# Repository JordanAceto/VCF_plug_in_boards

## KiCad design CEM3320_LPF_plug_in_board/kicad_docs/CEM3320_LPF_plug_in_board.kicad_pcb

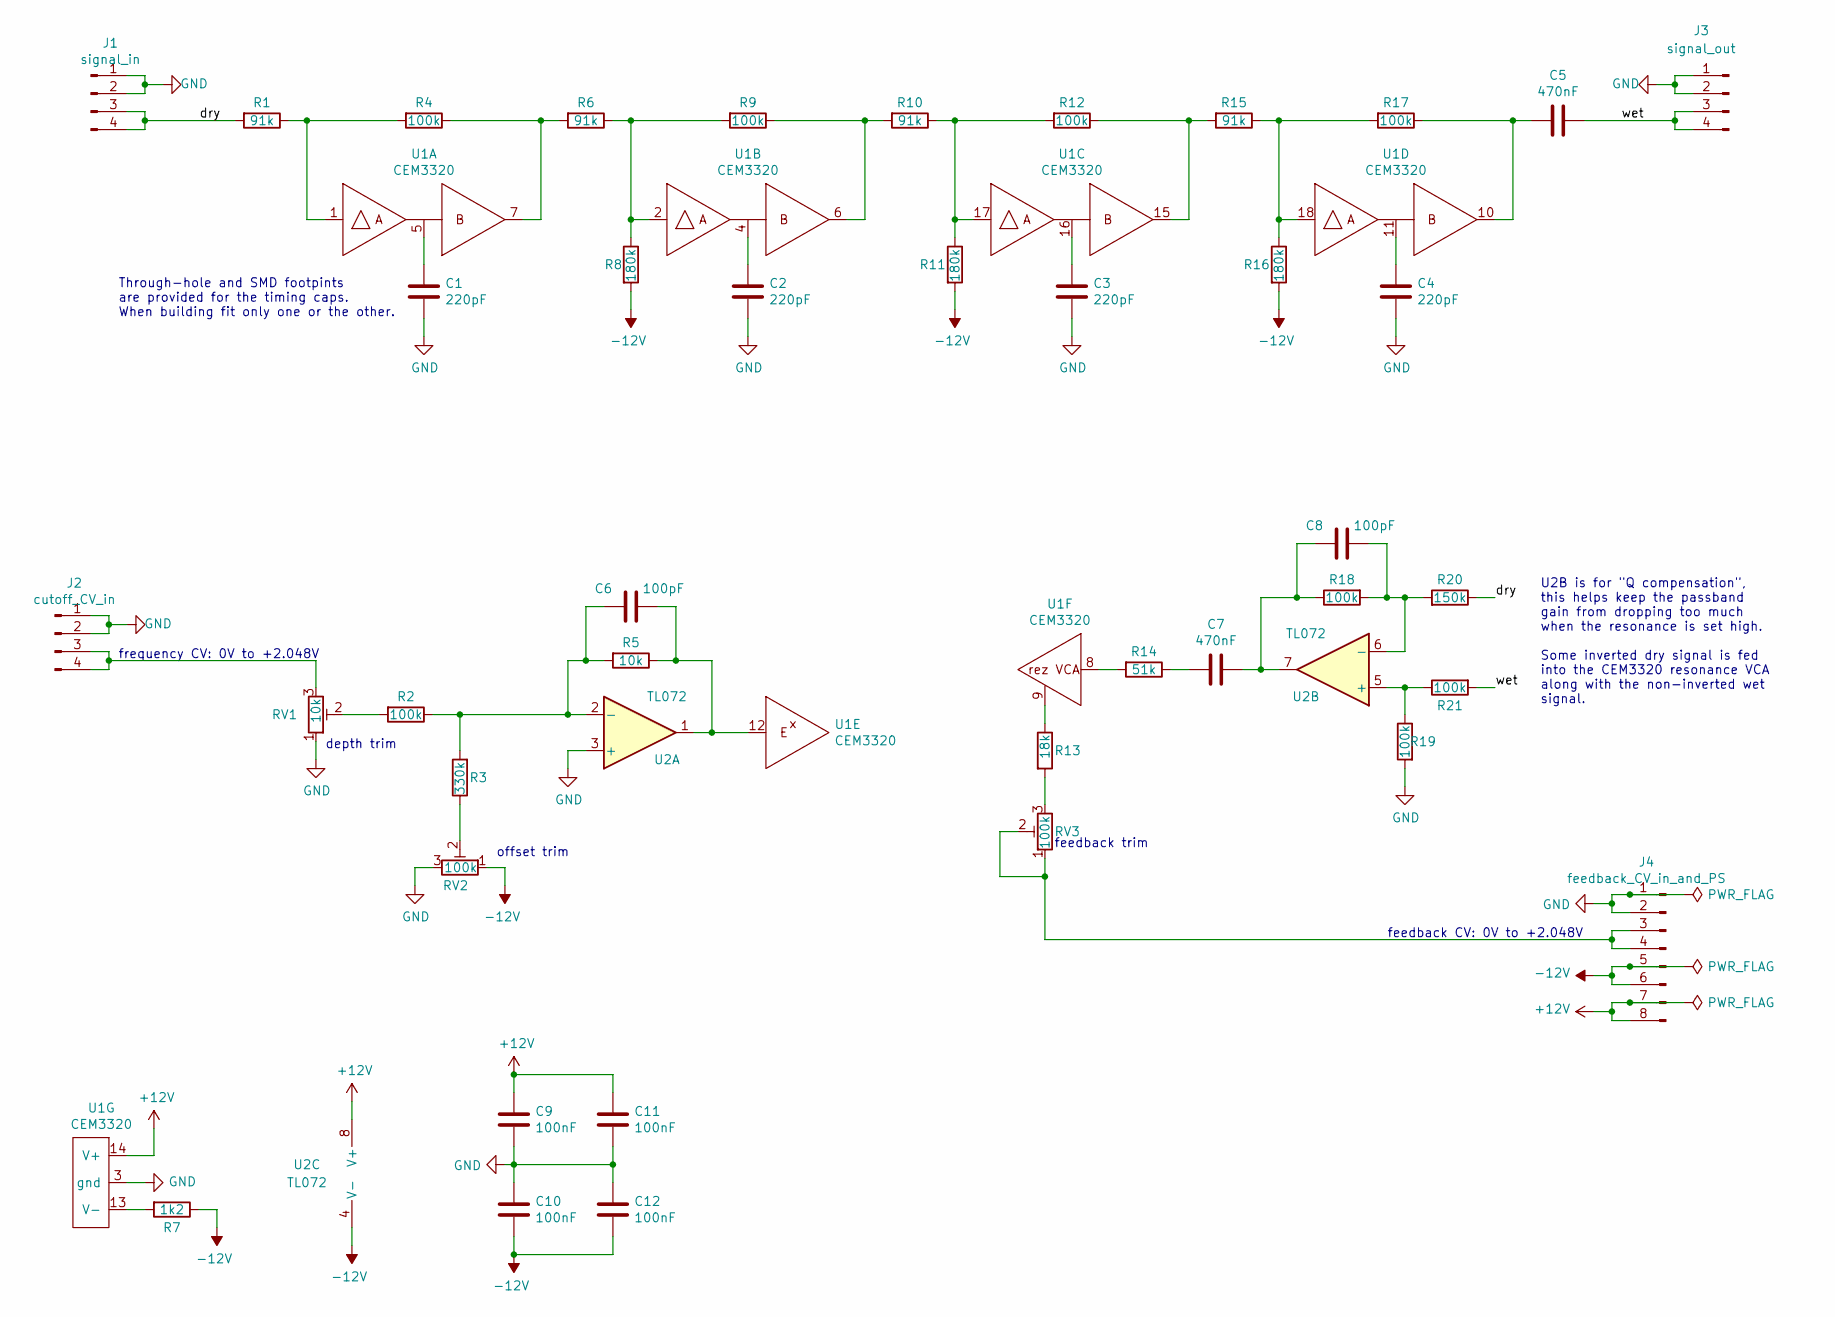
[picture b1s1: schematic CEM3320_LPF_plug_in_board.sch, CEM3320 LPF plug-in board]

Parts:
C1, C2, C3, C4: 220pF; timing_cap_dual_fp
C5, C7: 470nF; C_Rect_L7.0mm_W3.5mm_P5.00mm
C6, C8: 100pF; C_0805_2012Metric_Pad1.15x1.40mm_HandSolder
C9, C10, C11, C12: 100nF; C_0805_2012Metric_Pad1.15x1.40mm_HandSolder
J1: signal_in; PinHeader_1x04_P2.54mm_Vertical
J2: cutoff_CV_in; PinHeader_1x04_P2.54mm_Vertical
J3: signal_out; PinHeader_1x04_P2.54mm_Vertical
J4: feedback_CV_in_and_PS; PinHeader_1x08_P2.54mm_Vertical
R1, R6, R10, R15: 91k; R_0805_2012Metric_Pad1.15x1.40mm_HandSolder
R2, R4, R9, R12, R17, R18, R19, R21: 100k; R_0805_2012Metric_Pad1.15x1.40mm_HandSolder
R3: 330k; R_0805_2012Metric_Pad1.15x1.40mm_HandSolder
R5: 10k; R_0805_2012Metric_Pad1.15x1.40mm_HandSolder
R7: 1k2; R_0805_2012Metric_Pad1.15x1.40mm_HandSolder
R8, R11, R16: 180k; R_0805_2012Metric_Pad1.15x1.40mm_HandSolder
R13: 18k; R_0805_2012Metric_Pad1.15x1.40mm_HandSolder
R14: 51k; R_0805_2012Metric_Pad1.15x1.40mm_HandSolder
R20: 150k; R_0805_2012Metric_Pad1.15x1.40mm_HandSolder
RV1: 10k; Potentiometer_Bourns_3296W_Vertical
RV2, RV3: 100k; Potentiometer_Bourns_3296W_Vertical
U1: CEM3320; DIP-18_W7.62mm
U2: TL072; SOIC-8_3.9x4.9mm_P1.27mm

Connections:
+12V: C9.1, C11.1, J4.7, J4.8, U1.14 (V+), U2.8 (V+)
-12V: C10.2, C12.2, J4.5, J4.6, R7.1, R8.2, R11.2, R16.2, RV2.1, U2.4 (V-)
/dry: J1.3, J1.4, R1.2, R20.1
/wet: C5.1, J3.3, J3.4, R21.2
GND: C1.2, C2.2, C3.2, C4.2, C9.2, C10.1, C11.2, C12.1, J1.1, J1.2, J2.1, J2.2, J3.1, J3.2, J4.1, J4.2, R19.2, RV1.1, RV2.3, U1.3 (gnd), U2.3 (+)
unnamed: C1.1, U1.5
unnamed: C2.1, U1.4
unnamed: C3.1, U1.16
unnamed: C4.1, U1.11
unnamed: C5.2, R17.1, U1.10
unnamed: C6.1, R2.1, R3.2, R5.2, U2.2 (-)
unnamed: C6.2, R5.1, U1.12, U2.1
unnamed: C7.1, C8.1, R18.1, U2.7
unnamed: C7.2, R14.1
unnamed: C8.2, R18.2, R20.2, U2.6 (-)
unnamed: J2.3, J2.4, RV1.3
unnamed: J4.3, J4.4, RV3.1, RV3.2
unnamed: R1.1, R4.2, U1.1
unnamed: R2.2, RV1.2
unnamed: R3.1, RV2.2
unnamed: R4.1, R6.2, U1.7
unnamed: R6.1, R8.1, R9.2, U1.2
unnamed: R7.2, U1.13 (V-)
unnamed: R10.1, R11.1, R12.2, U1.17
unnamed: R9.1, R10.2, U1.6
unnamed: R12.1, R15.2, U1.15
unnamed: R13.1, U1.9
unnamed: R13.2, RV3.3
unnamed: R14.2, U1.8
unnamed: R15.1, R16.1, R17.2, U1.18
unnamed: R19.1, R21.1, U2.5 (+)

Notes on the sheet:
feedback CV: 0V to +2.048V
frequency CV: 0V to +2.048V
U2B is for "Q compensation", this helps keep the passband gain from dropping too much when the resonance is set high. Some inverted dry signal is fed into the CEM3320 resonance VCA along with the non-inverted wet signal.
feedback trim
depth trim
offset trim
Through-hole and SMD footpints are provided for the timing caps. When building fit only one or the other.

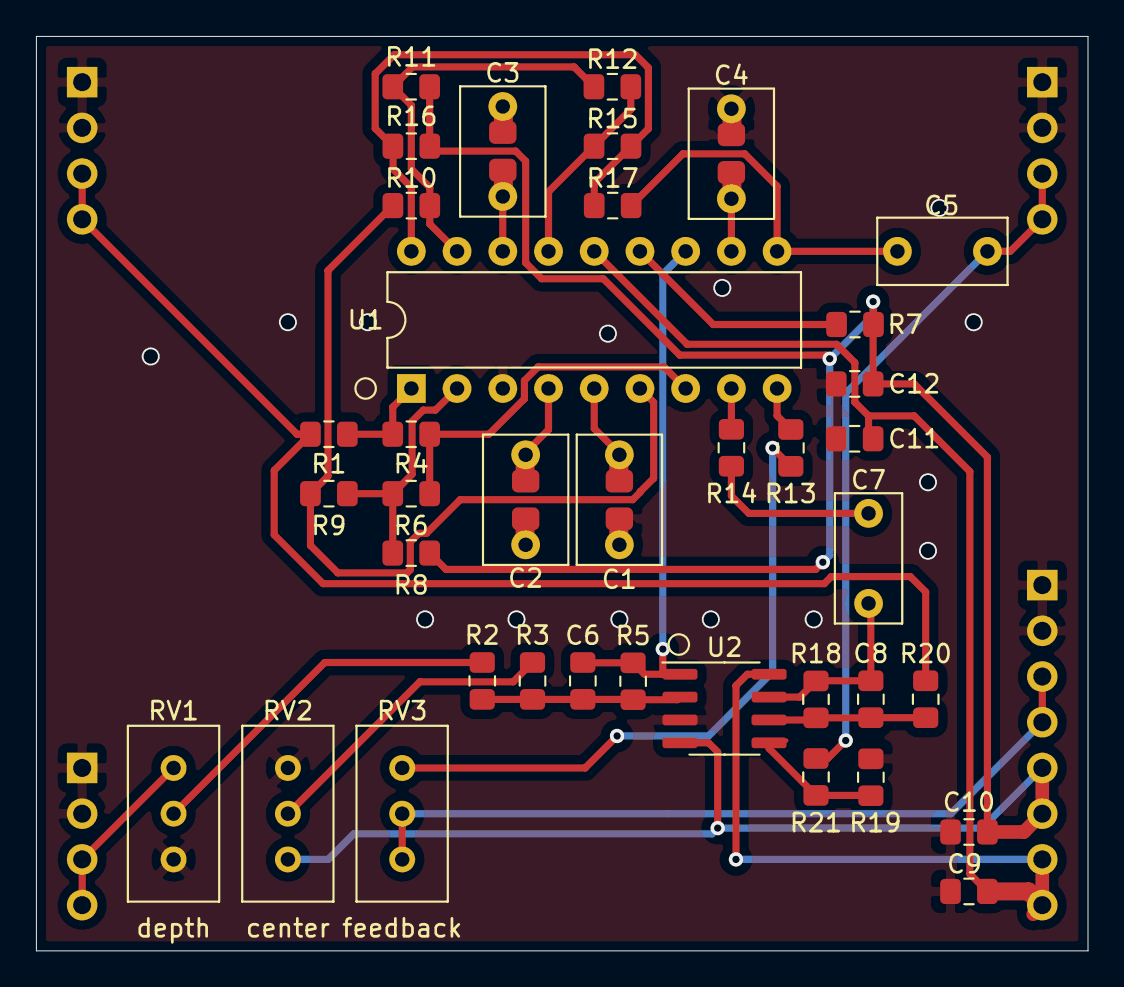
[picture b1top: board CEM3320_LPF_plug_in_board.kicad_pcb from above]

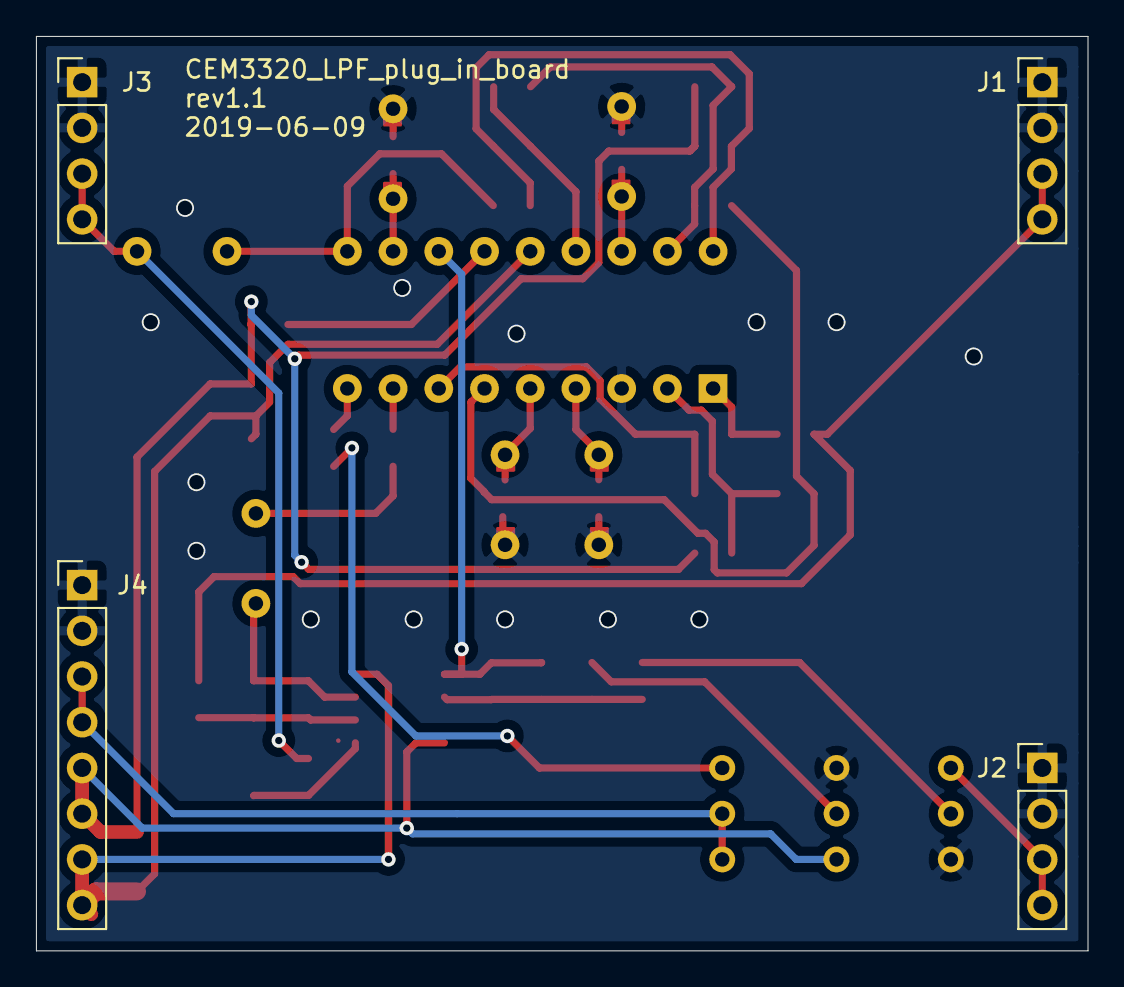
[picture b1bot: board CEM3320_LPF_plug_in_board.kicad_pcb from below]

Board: 2 copper layers, 58.4 x 50.8 mm, 42 parts (4 on the bottom side), 31 nets.

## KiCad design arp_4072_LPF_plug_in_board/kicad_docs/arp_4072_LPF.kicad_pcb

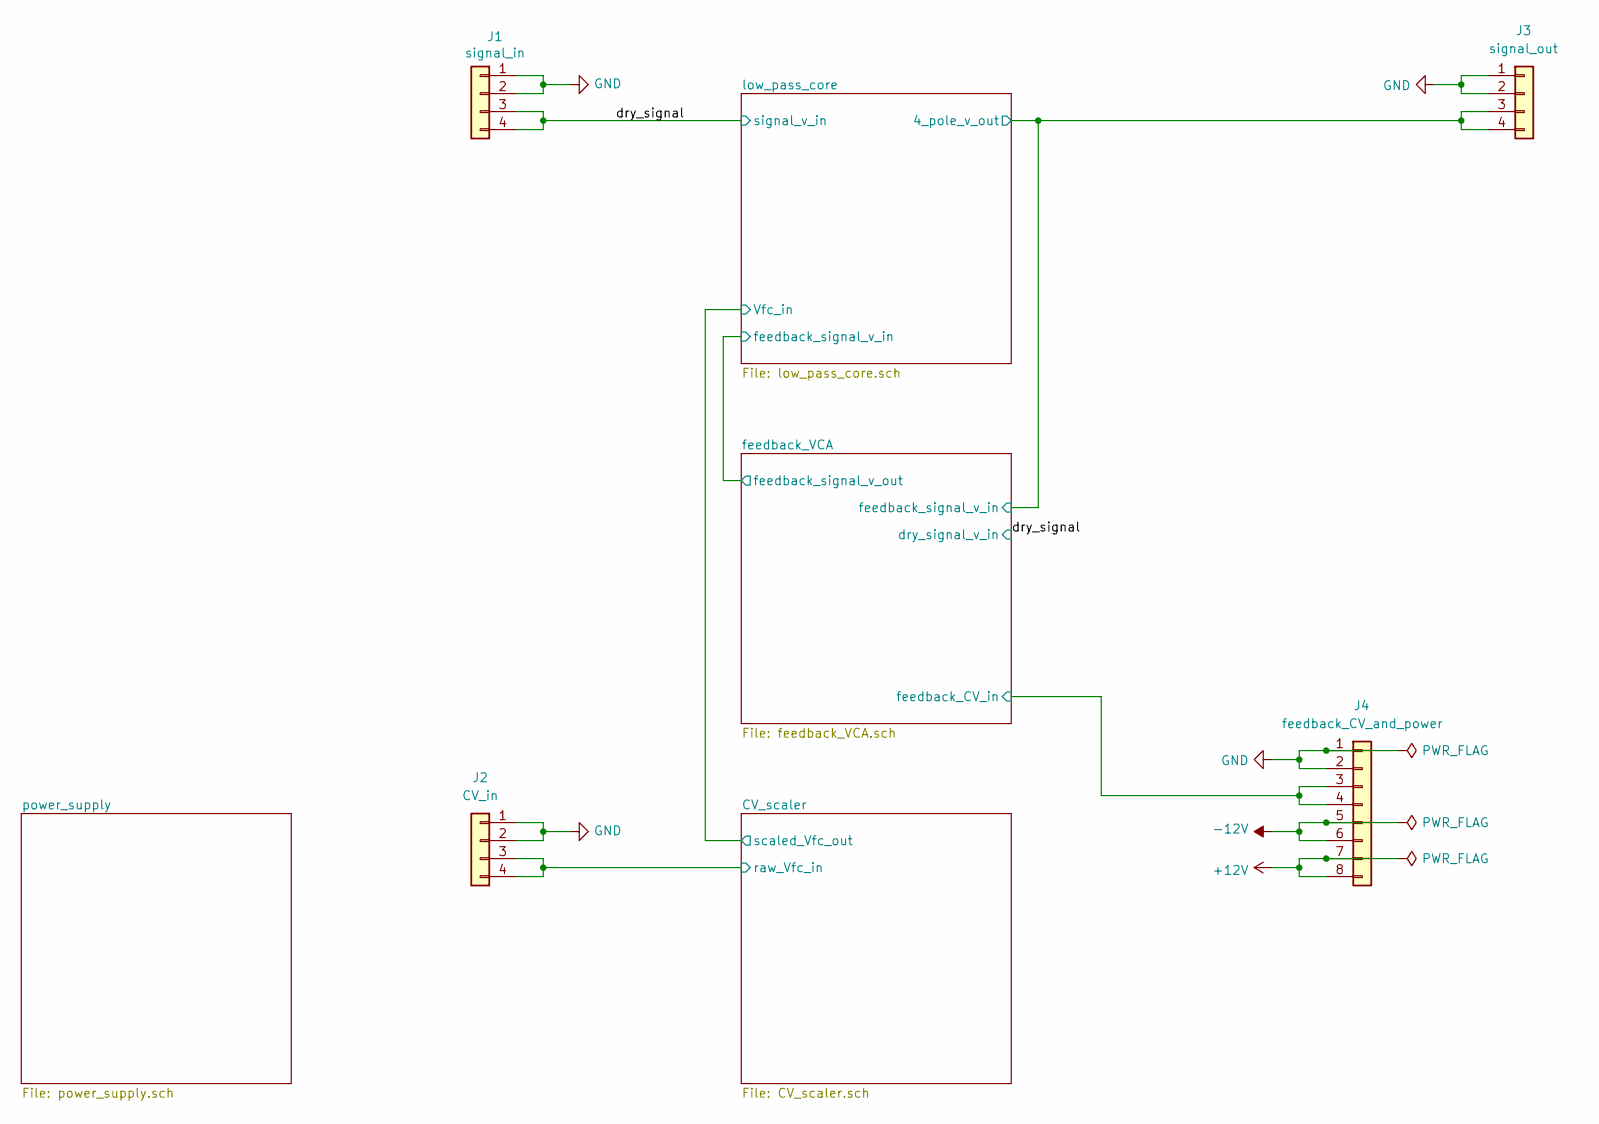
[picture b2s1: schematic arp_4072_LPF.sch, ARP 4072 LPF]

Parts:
J1: signal_in; PinHeader_1x04_P2.54mm_Vertical
J2: CV_in; PinHeader_1x04_P2.54mm_Vertical
J3: signal_out; PinHeader_1x04_P2.54mm_Vertical
J4: feedback_CV_and_power; PinHeader_1x08_P2.54mm_Vertical

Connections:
+12V: J4.7, J4.8; also elsewhere on the board
-12V: J4.5, J4.6; also elsewhere on the board
/CV_scaler/raw_Vfc_in: J2.3, J2.4; also elsewhere on the board
/dry_signal: J1.3, J1.4; also elsewhere on the board
/feedback_VCA/feedback_CV_in: J4.3, J4.4; also elsewhere on the board
/low_pass_core/4_pole_v_out: J3.3, J3.4; also elsewhere on the board
GND: J1.1, J1.2, J2.1, J2.2, J3.1, J3.2, J4.1, J4.2; also elsewhere on the board

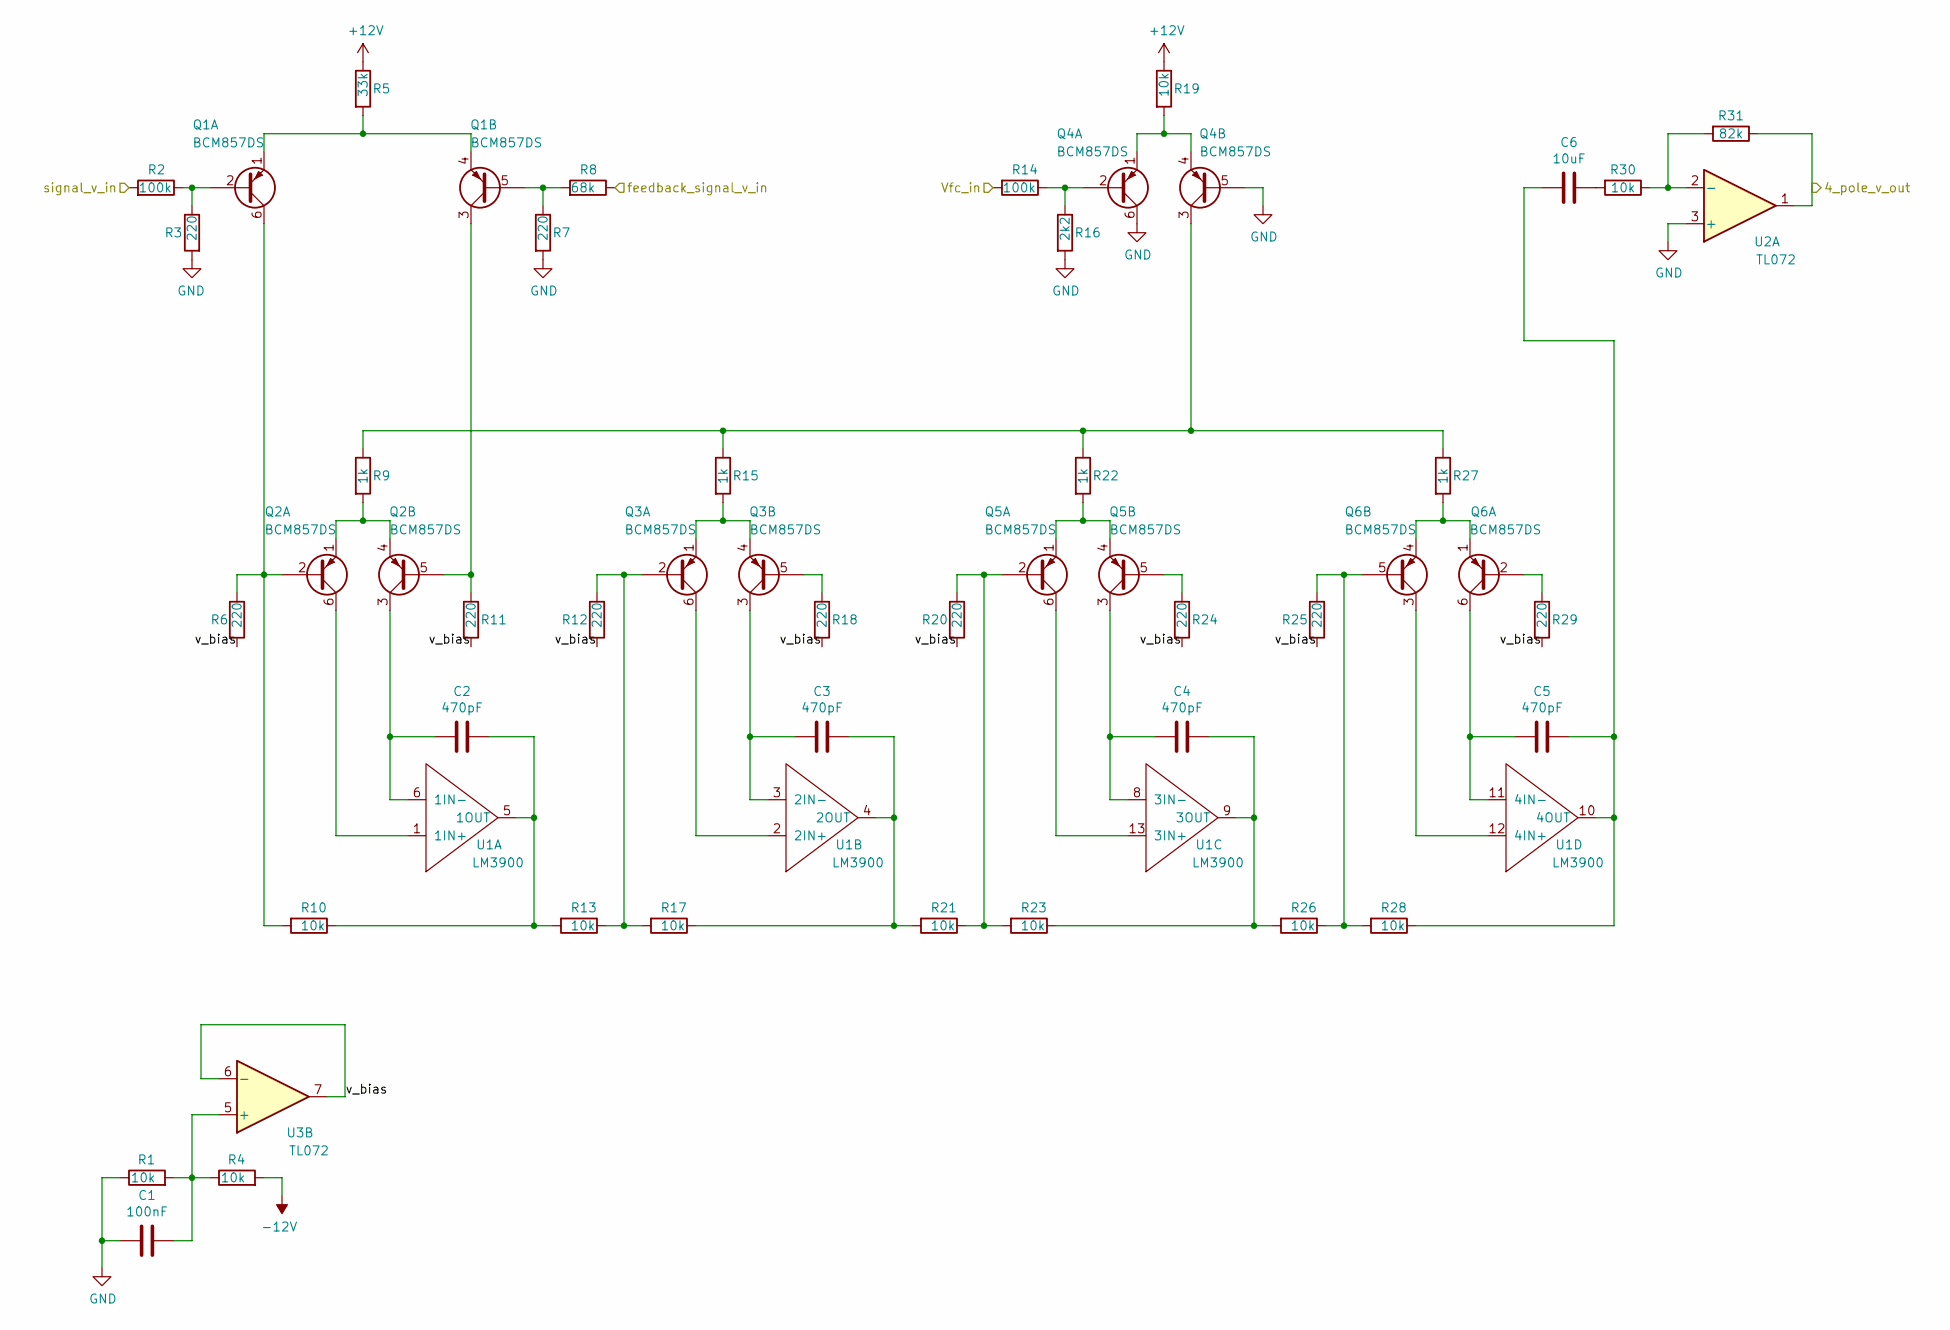
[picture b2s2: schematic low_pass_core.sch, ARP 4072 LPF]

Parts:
C1: 100nF; C_0805_2012Metric_Pad1.15x1.40mm_HandSolder
C2, C3, C4, C5: 470pF; C_0805_2012Metric_Pad1.15x1.40mm_HandSolder
C6: 10uF; CP_Radial_D6.3mm_P2.50mm
Q1, Q2, Q3, Q4, Q5, Q6: BCM857DS; SOT457
R1, R4, R10, R13, R17, R19, R21, R23, R26, R28, R30: 10k; R_0805_2012Metric_Pad1.15x1.40mm_HandSolder
R2, R14: 100k; R_0805_2012Metric_Pad1.15x1.40mm_HandSolder
R3, R6, R7, R11, R12, R18, R20, R24, R25, R29: 220; R_0805_2012Metric_Pad1.15x1.40mm_HandSolder
R5: 33k; R_0805_2012Metric_Pad1.15x1.40mm_HandSolder
R8: 68k; R_0805_2012Metric_Pad1.15x1.40mm_HandSolder
R9, R15, R22, R27: 1k; R_0805_2012Metric_Pad1.15x1.40mm_HandSolder
R16: 2k2; R_0805_2012Metric_Pad1.15x1.40mm_HandSolder
R31: 82k; R_0805_2012Metric_Pad1.15x1.40mm_HandSolder
U1: LM3900; SOIC-14_3.9x8.7mm_P1.27mm
U2, U3: TL072; SOIC-8_3.9x4.9mm_P1.27mm

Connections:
+12V: R5.1, R19.1; also elsewhere on the board
-12V: R4.2; also elsewhere on the board
/dry_signal: R2.2; also elsewhere on the board
/low_pass_core/4_pole_v_out: R31.1, U2.1; also elsewhere on the board
/low_pass_core/Vfc_in: R14.2; also elsewhere on the board
/low_pass_core/feedback_signal_v_in: R8.1; also elsewhere on the board
/low_pass_core/v_bias: R6.2, R11.2, R12.2, R18.2, R20.2, R24.2, R25.2, R29.2, U3.6 (-), U3.7
GND: C1.2, Q4.5 (B), Q4.6 (C), R1.1, R3.2, R7.2, R16.2, U2.3 (+); also elsewhere on the board
unnamed: C1.1, R1.2, R4.1, U3.5 (+)
unnamed: C2.1, R10.1, R13.2, U1.5 (1OUT)
unnamed: C2.2, Q2.3 (C), U1.6 (1IN-)
unnamed: C3.1, R17.1, R21.2, U1.4 (2OUT)
unnamed: C3.2, Q3.3 (C), U1.3 (2IN-)
unnamed: C4.1, R23.1, R26.2, U1.9 (3OUT)
unnamed: C4.2, Q5.3 (C), U1.8 (3IN-)
unnamed: C5.1, C6.2, R28.1, U1.10 (4OUT)
unnamed: C5.2, Q6.6 (C), U1.11 (4IN-)
unnamed: C6.1, R30.2
unnamed: Q1.1 (E), Q1.4 (E), R5.2
unnamed: Q1.2 (B), R2.1, R3.1
unnamed: Q1.3 (C), Q2.5 (B), R11.1
unnamed: Q1.5 (B), R7.1, R8.2
unnamed: Q1.6 (C), Q2.2 (B), R6.1, R10.2
unnamed: Q2.1 (E), Q2.4 (E), R9.2
unnamed: Q2.6 (C), U1.1 (1IN+)
unnamed: Q3.1 (E), Q3.4 (E), R15.2
unnamed: Q3.2 (B), R12.1, R13.1, R17.2
unnamed: Q3.5 (B), R18.1
unnamed: Q3.6 (C), U1.2 (2IN+)
unnamed: Q4.1 (E), Q4.4 (E), R19.2
unnamed: Q4.2 (B), R14.1, R16.1
unnamed: Q4.3 (C), R9.1, R15.1, R22.1, R27.1
unnamed: Q5.1 (E), Q5.4 (E), R22.2
unnamed: Q5.2 (B), R20.1, R21.1, R23.2
unnamed: Q5.5 (B), R24.1
unnamed: Q5.6 (C), U1.13 (3IN+)
unnamed: Q6.1 (E), Q6.4 (E), R27.2
unnamed: Q6.2 (B), R29.1
unnamed: Q6.3 (C), U1.12 (4IN+)
unnamed: Q6.5 (B), R25.1, R26.1, R28.2
unnamed: R30.1, R31.2, U2.2 (-)

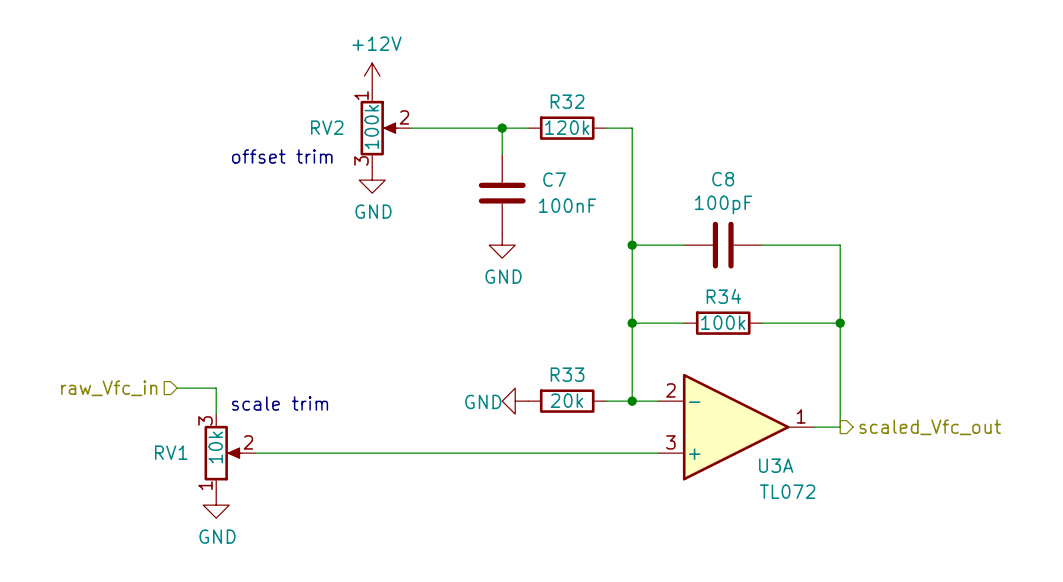
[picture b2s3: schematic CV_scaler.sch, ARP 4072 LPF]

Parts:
C7: 100nF; C_0805_2012Metric_Pad1.15x1.40mm_HandSolder
C8: 100pF; C_0805_2012Metric_Pad1.15x1.40mm_HandSolder
R32: 120k; R_0805_2012Metric_Pad1.15x1.40mm_HandSolder
R33: 20k; R_0805_2012Metric_Pad1.15x1.40mm_HandSolder
R34: 100k; R_0805_2012Metric_Pad1.15x1.40mm_HandSolder
RV1: 10k; Potentiometer_Bourns_3296W_Vertical
RV2: 100k; Potentiometer_Bourns_3296W_Vertical
U3: TL072; SOIC-8_3.9x4.9mm_P1.27mm

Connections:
+12V: RV2.1; also elsewhere on the board
/CV_scaler/raw_Vfc_in: RV1.3; also elsewhere on the board
/low_pass_core/Vfc_in: C8.1, R34.1, U3.1; also elsewhere on the board
GND: C7.1, R33.2, RV1.1, RV2.3; also elsewhere on the board
unnamed: C7.2, R32.2, RV2.2
unnamed: C8.2, R32.1, R33.1, R34.2, U3.2 (-)
unnamed: RV1.2, U3.3 (+)

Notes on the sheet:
scale trim
offset trim

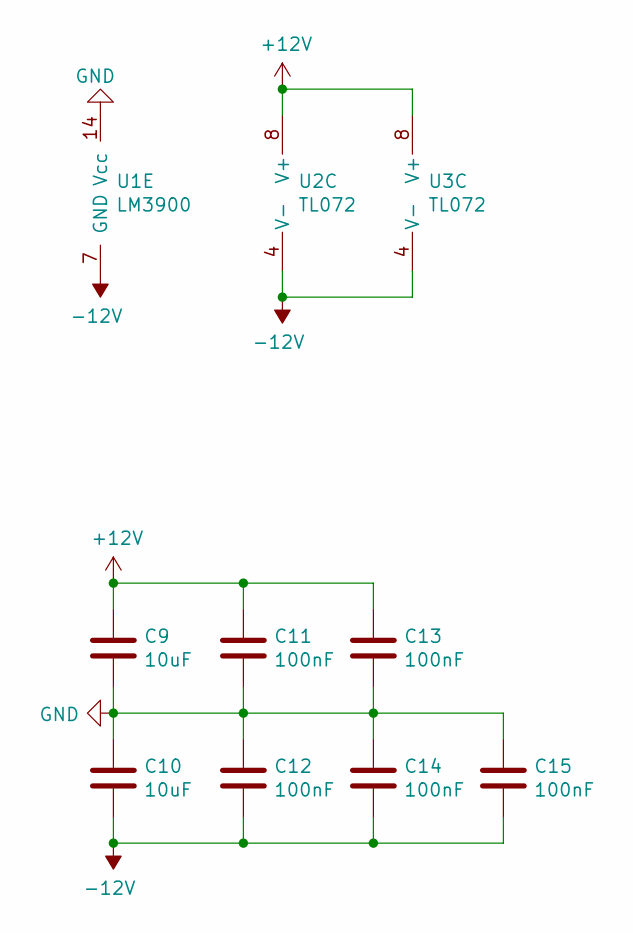
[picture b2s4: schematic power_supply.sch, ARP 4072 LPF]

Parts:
C9, C10: 10uF; C_0805_2012Metric_Pad1.15x1.40mm_HandSolder
C11, C12, C13, C14, C15: 100nF; C_0805_2012Metric_Pad1.15x1.40mm_HandSolder
U1: LM3900; SOIC-14_3.9x8.7mm_P1.27mm
U2, U3: TL072; SOIC-8_3.9x4.9mm_P1.27mm

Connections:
+12V: C9.1, C11.1, C13.1, U2.8 (V+), U3.8 (V+); also elsewhere on the board
-12V: C10.2, C12.2, C14.2, C15.2, U1.7 (GND), U2.4 (V-), U3.4 (V-); also elsewhere on the board
GND: C9.2, C10.1, C11.2, C12.1, C13.2, C14.1, C15.1, U1.14 (Vcc); also elsewhere on the board

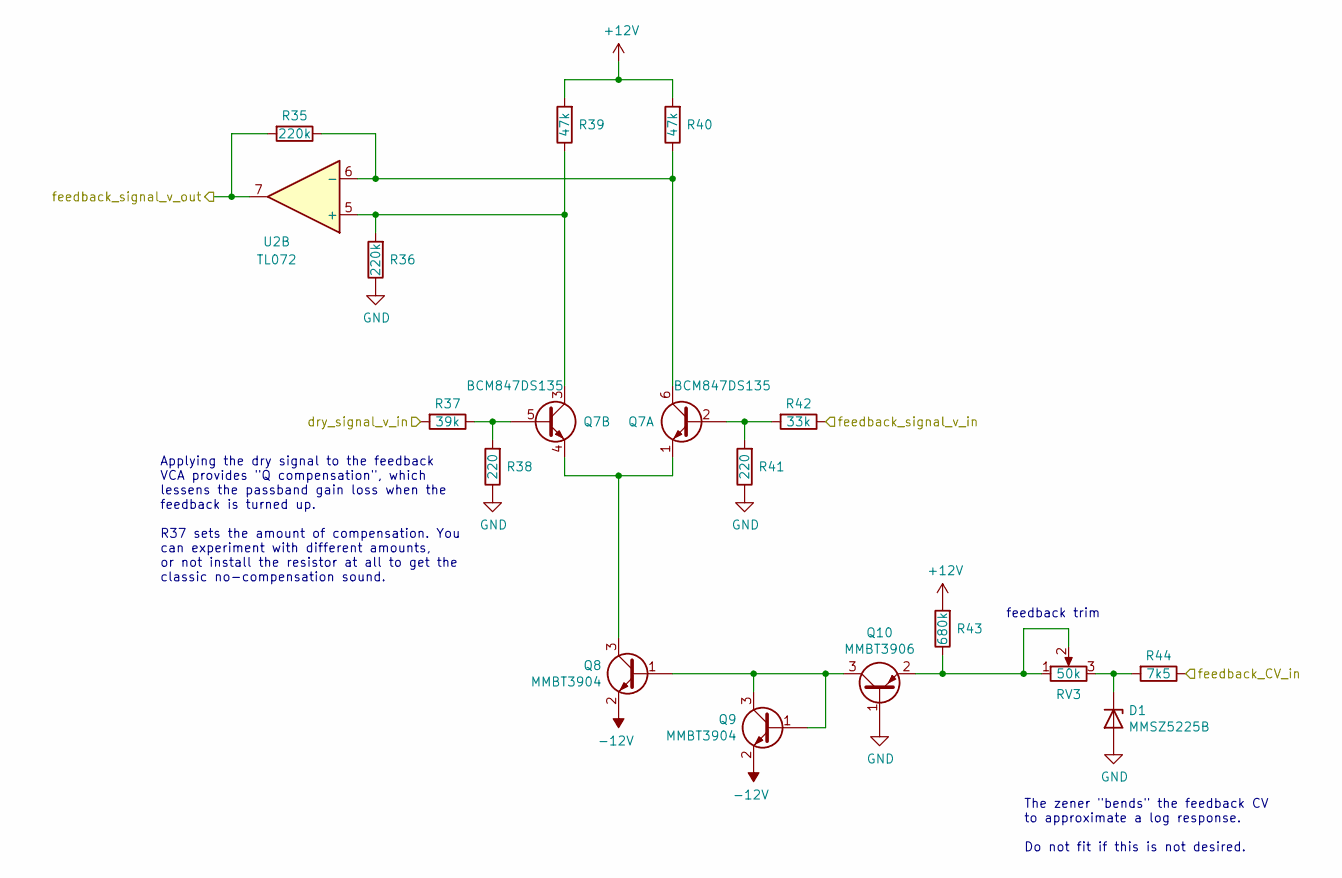
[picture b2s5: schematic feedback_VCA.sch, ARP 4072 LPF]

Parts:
D1: MMSZ5225B; D_SOD-123
Q7: BCM847DS135; SOT457
Q8, Q9: MMBT3904; SOT-23_Handsoldering
Q10: MMBT3906; SOT-23_Handsoldering
R35, R36: 220k; R_0805_2012Metric_Pad1.15x1.40mm_HandSolder
R37: 39k; R_0805_2012Metric_Pad1.15x1.40mm_HandSolder
R38, R41: 220; R_0805_2012Metric_Pad1.15x1.40mm_HandSolder
R39, R40: 47k; R_0805_2012Metric_Pad1.15x1.40mm_HandSolder
R42: 33k; R_0805_2012Metric_Pad1.15x1.40mm_HandSolder
R43: 680k; R_0805_2012Metric_Pad1.15x1.40mm_HandSolder
R44: 7k5; R_0805_2012Metric_Pad1.15x1.40mm_HandSolder
RV3: 50k; Potentiometer_Bourns_3296W_Vertical
U2: TL072; SOIC-8_3.9x4.9mm_P1.27mm

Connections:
+12V: R39.2, R40.2, R43.2; also elsewhere on the board
-12V: Q8.2 (E), Q9.2 (E); also elsewhere on the board
/dry_signal: R37.2; also elsewhere on the board
/feedback_VCA/feedback_CV_in: R44.1; also elsewhere on the board
/low_pass_core/4_pole_v_out: R42.1; also elsewhere on the board
/low_pass_core/feedback_signal_v_in: R35.2, U2.7; also elsewhere on the board
GND: D1.2 (A), Q10.1 (B), R36.1, R38.1, R41.1; also elsewhere on the board
unnamed: D1.1 (K), R44.2, RV3.3
unnamed: Q7.1 (E), Q7.4 (E), Q8.3 (C)
unnamed: Q7.2 (B), R41.2, R42.2
unnamed: Q7.3 (C), R36.2, R39.1, U2.5 (+)
unnamed: Q7.5 (B), R37.1, R38.2
unnamed: Q7.6 (C), R35.1, R40.1, U2.6 (-)
unnamed: Q10.2 (E), R43.1, RV3.1, RV3.2
unnamed: Q8.1 (B), Q9.1 (B), Q9.3 (C), Q10.3 (C)

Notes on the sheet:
The zener "bends" the feedback CV to approximate a log response. Do not fit if this is not desired.
feedback trim
Applying the dry signal to the feedback VCA provides "Q compensation", which lessens the passband gain loss when the feedback is turned up. R37 sets the amount of compensation. You can experiment with different amounts, or not install the resistor at all to get the classic no-compensation sound.

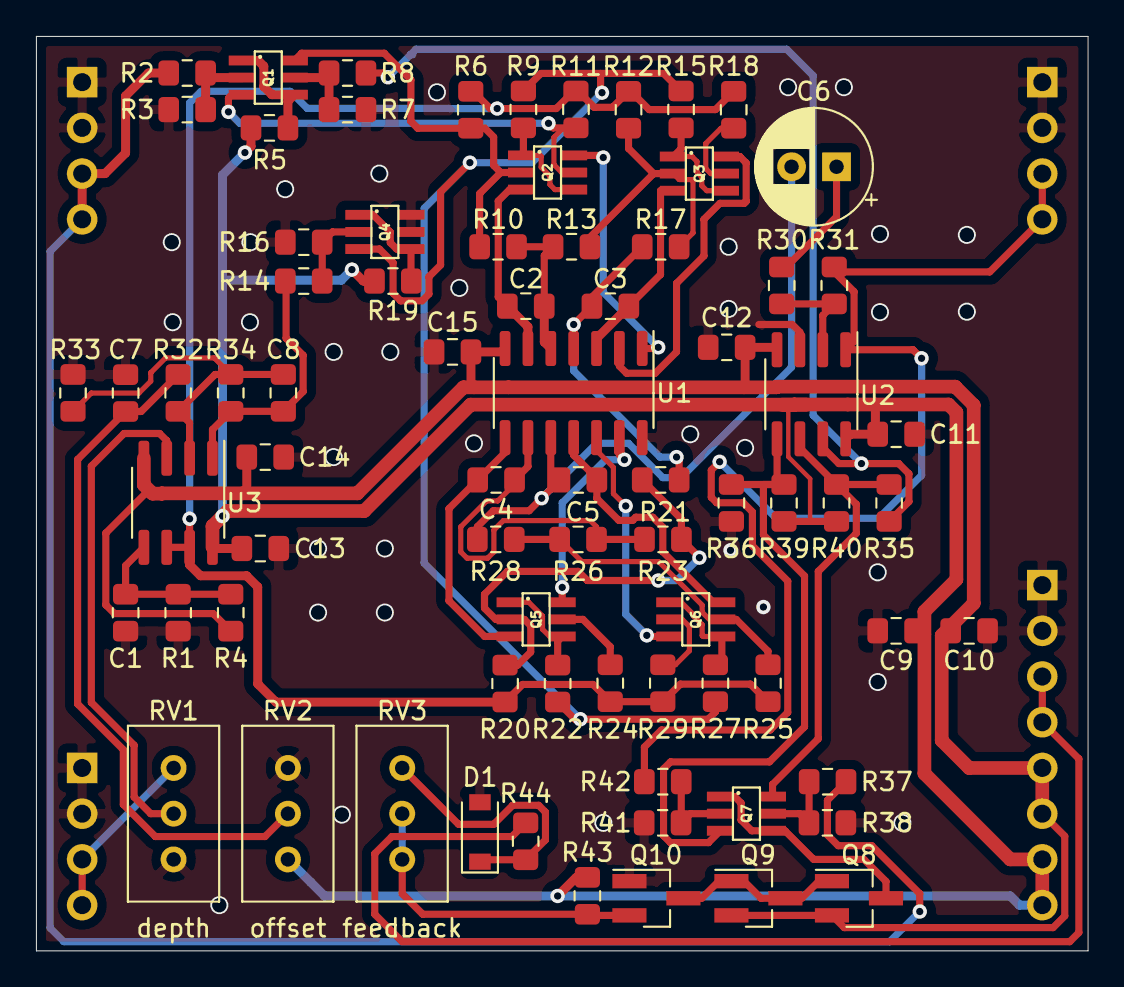
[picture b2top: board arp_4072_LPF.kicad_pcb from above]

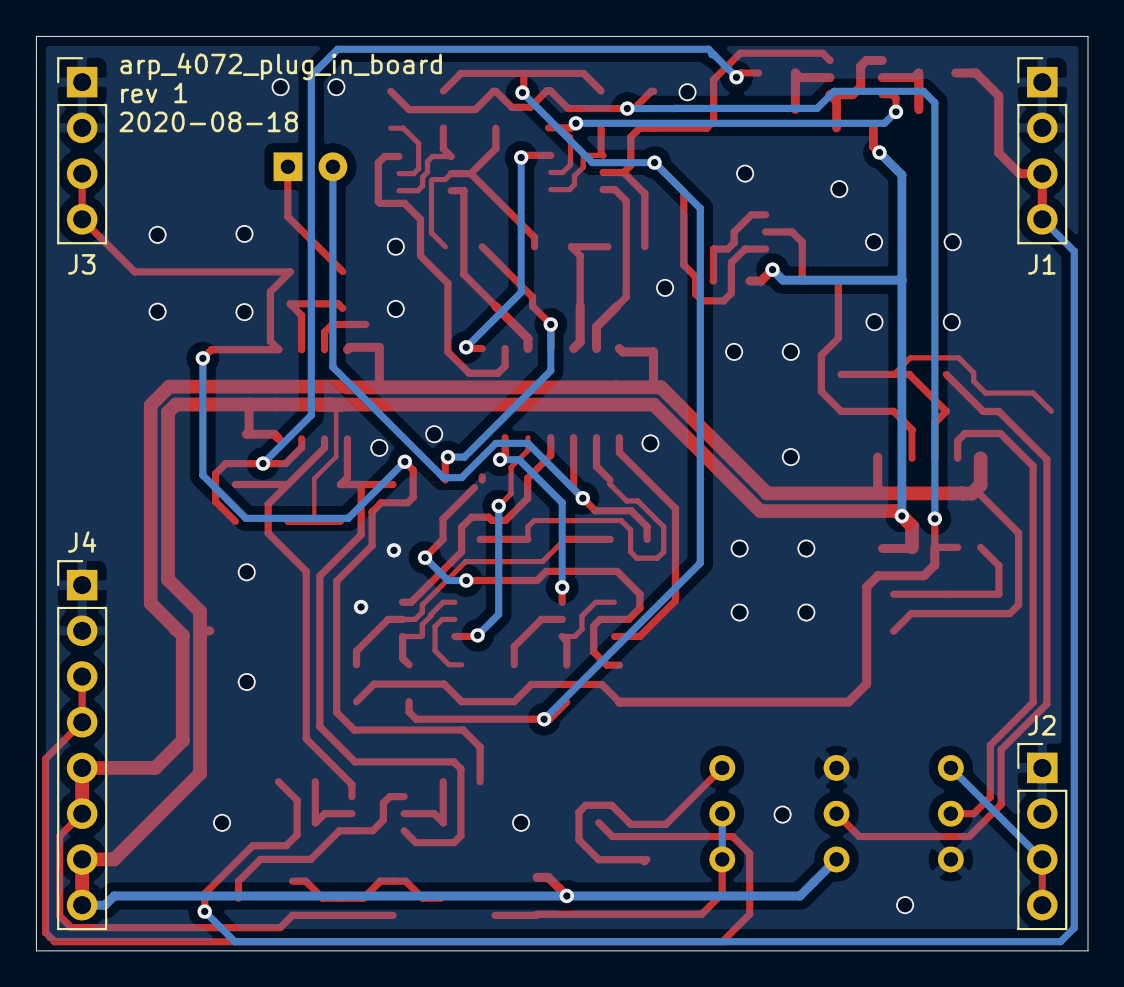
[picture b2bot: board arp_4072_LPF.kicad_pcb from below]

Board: 2 copper layers, 58.4 x 50.8 mm, 80 parts (4 on the bottom side), 54 nets.

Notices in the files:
CEM3320_LPF_plug_in_board/kicad_docs/CEM3320_LPF_plug_in_board.kicad_pcb:
License: CC by 4.0
CEM3320_LPF_plug_in_board/kicad_docs/CEM3320_LPF_plug_in_board.sch:
creativecommons.org/licenses/by/4.0
optical_phasor_plug_in_board/kicad_docs/optical_phasor_plug_in_board.kicad_pcb:
Licinse: CC by 4.0
